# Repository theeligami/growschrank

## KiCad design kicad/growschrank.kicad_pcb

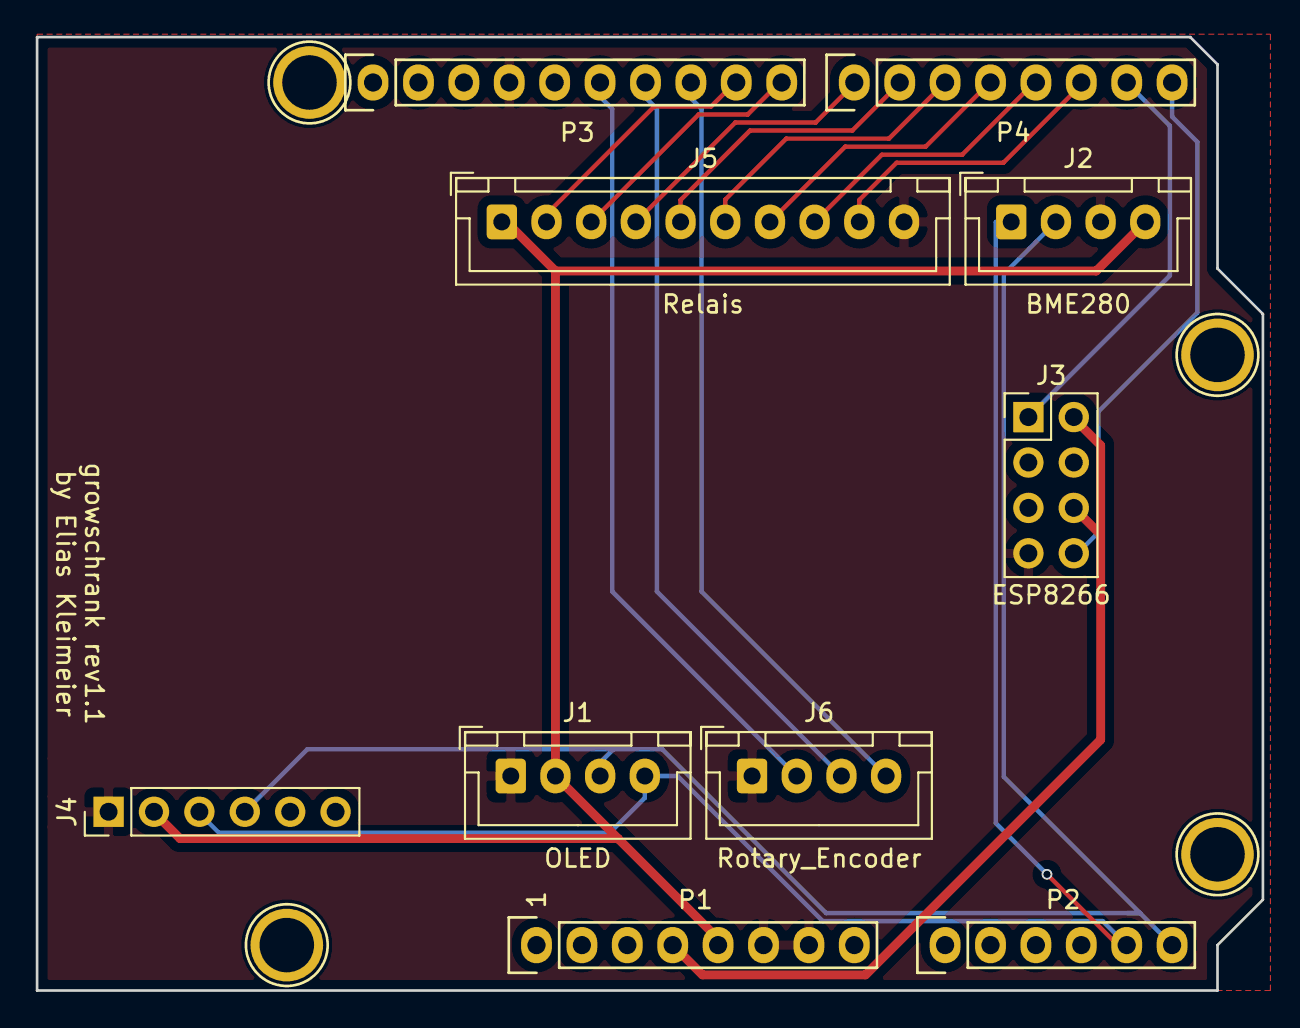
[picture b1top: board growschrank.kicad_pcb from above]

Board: 2 copper layers, 68.6 x 53.3 mm, 14 parts (0 on the bottom side), 18 nets.

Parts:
J1: OLED; JST_XH_B4B-XH-A_1x04_P2.50mm_Vertical
J2: BME280; JST_XH_B4B-XH-A_1x04_P2.50mm_Vertical
J3: ESP8266; PinHeader_2x04_P2.54mm_Vertical
J4: DS3231; PinHeader_1x06_P2.54mm_Vertical
J5: Relais; JST_XH_B10B-XH-A_1x10_P2.50mm_Vertical
J6: Rotary_Encoder; JST_XH_B4B-XH-A_1x04_P2.50mm_Vertical
P1: Power; Socket_Strip_Arduino_1x08
P2: Analog; Socket_Strip_Arduino_1x06
P3: Digital; Socket_Strip_Arduino_1x10
P4: Digital; Socket_Strip_Arduino_1x08
P5, P6, P7, P8: CONN_01X01; Arduino_1pin

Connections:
+3V3: J3.2, J3.6, P1.4
+5V: J1.2, J2.4, J4.2, J5.1, P1.5
/0(Rx): J3.8, P4.8
/1(Tx): J3.1, P4.7
/2: J5.9, P4.6
/3(**): J5.8, P4.5
/4: J5.7, P4.4
/5(**): J5.6, P4.3
/6(**): J5.5, P4.2
/7: J5.4, P4.1
/8: J5.3, P3.10
/9(**): J5.2, P3.9
/10(**/SS): J6.4, P3.8
/11(**/MOSI): J6.3, P3.7
/12(MISO): J6.2, P3.6
/A4(SDA): J1.4, J2.1, J4.3, P2.5, P3.2
/A5(SCL): J1.3, J2.2, J4.4, P2.6, P3.1
GND: J1.1, J2.3, J3.7, J4.1, J5.10, J6.1, P1.6, P1.7, P3.4

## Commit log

2020-11-20 Added dependencies
2020-12-16 Added test stuff and interrupt vector
2020-12-19 Added partial menu functionality and visuals. Also clock should work now
2020-12-20 Added EEPROM. Menus working now.
2020-12-20 Added timer functionality.
2020-12-20 Added energy saving for screen
2020-12-21 Fixed power supply of BME280
2020-12-21 Added BME280 functionality
2020-12-21 Ignore .swp files
2020-12-21 Did some cleanup
2020-12-21 Removed redundancy
2020-12-22 GY-BME280 is 3.3V-5V fuck this shit
2020-12-22 Added BME280
2020-12-22 Cleaned up + added manual control mode
2020-12-30 Changed relais connector
2020-12-30 Added plans for wiring
2021-01-07 Added DIN Rail case for relais
2021-01-07 Added more space for clock
2021-01-31 Stuff
2021-01-31 Moved to CAD
2021-01-31 3d model for relais
2021-04-16 Adjustments because relay is active low
2021-04-23 Added pin status to manual control
2021-05-19 Fixed debouncing issue
2021-09-16 Relays now remember state during blackout (if triggered automatically, manual mode is not affected)
2021-09-16 Fixed typo
2021-09-16 Bugfixing fuckery
2021-10-30 Adapter für Pumpe in Bewässerung hinzugefügt
2021-10-30 Fixed some stuff
2021-10-30 Lüfter funzt jetzt
2021-11-26 Adapter für Lüfterzuleitung
